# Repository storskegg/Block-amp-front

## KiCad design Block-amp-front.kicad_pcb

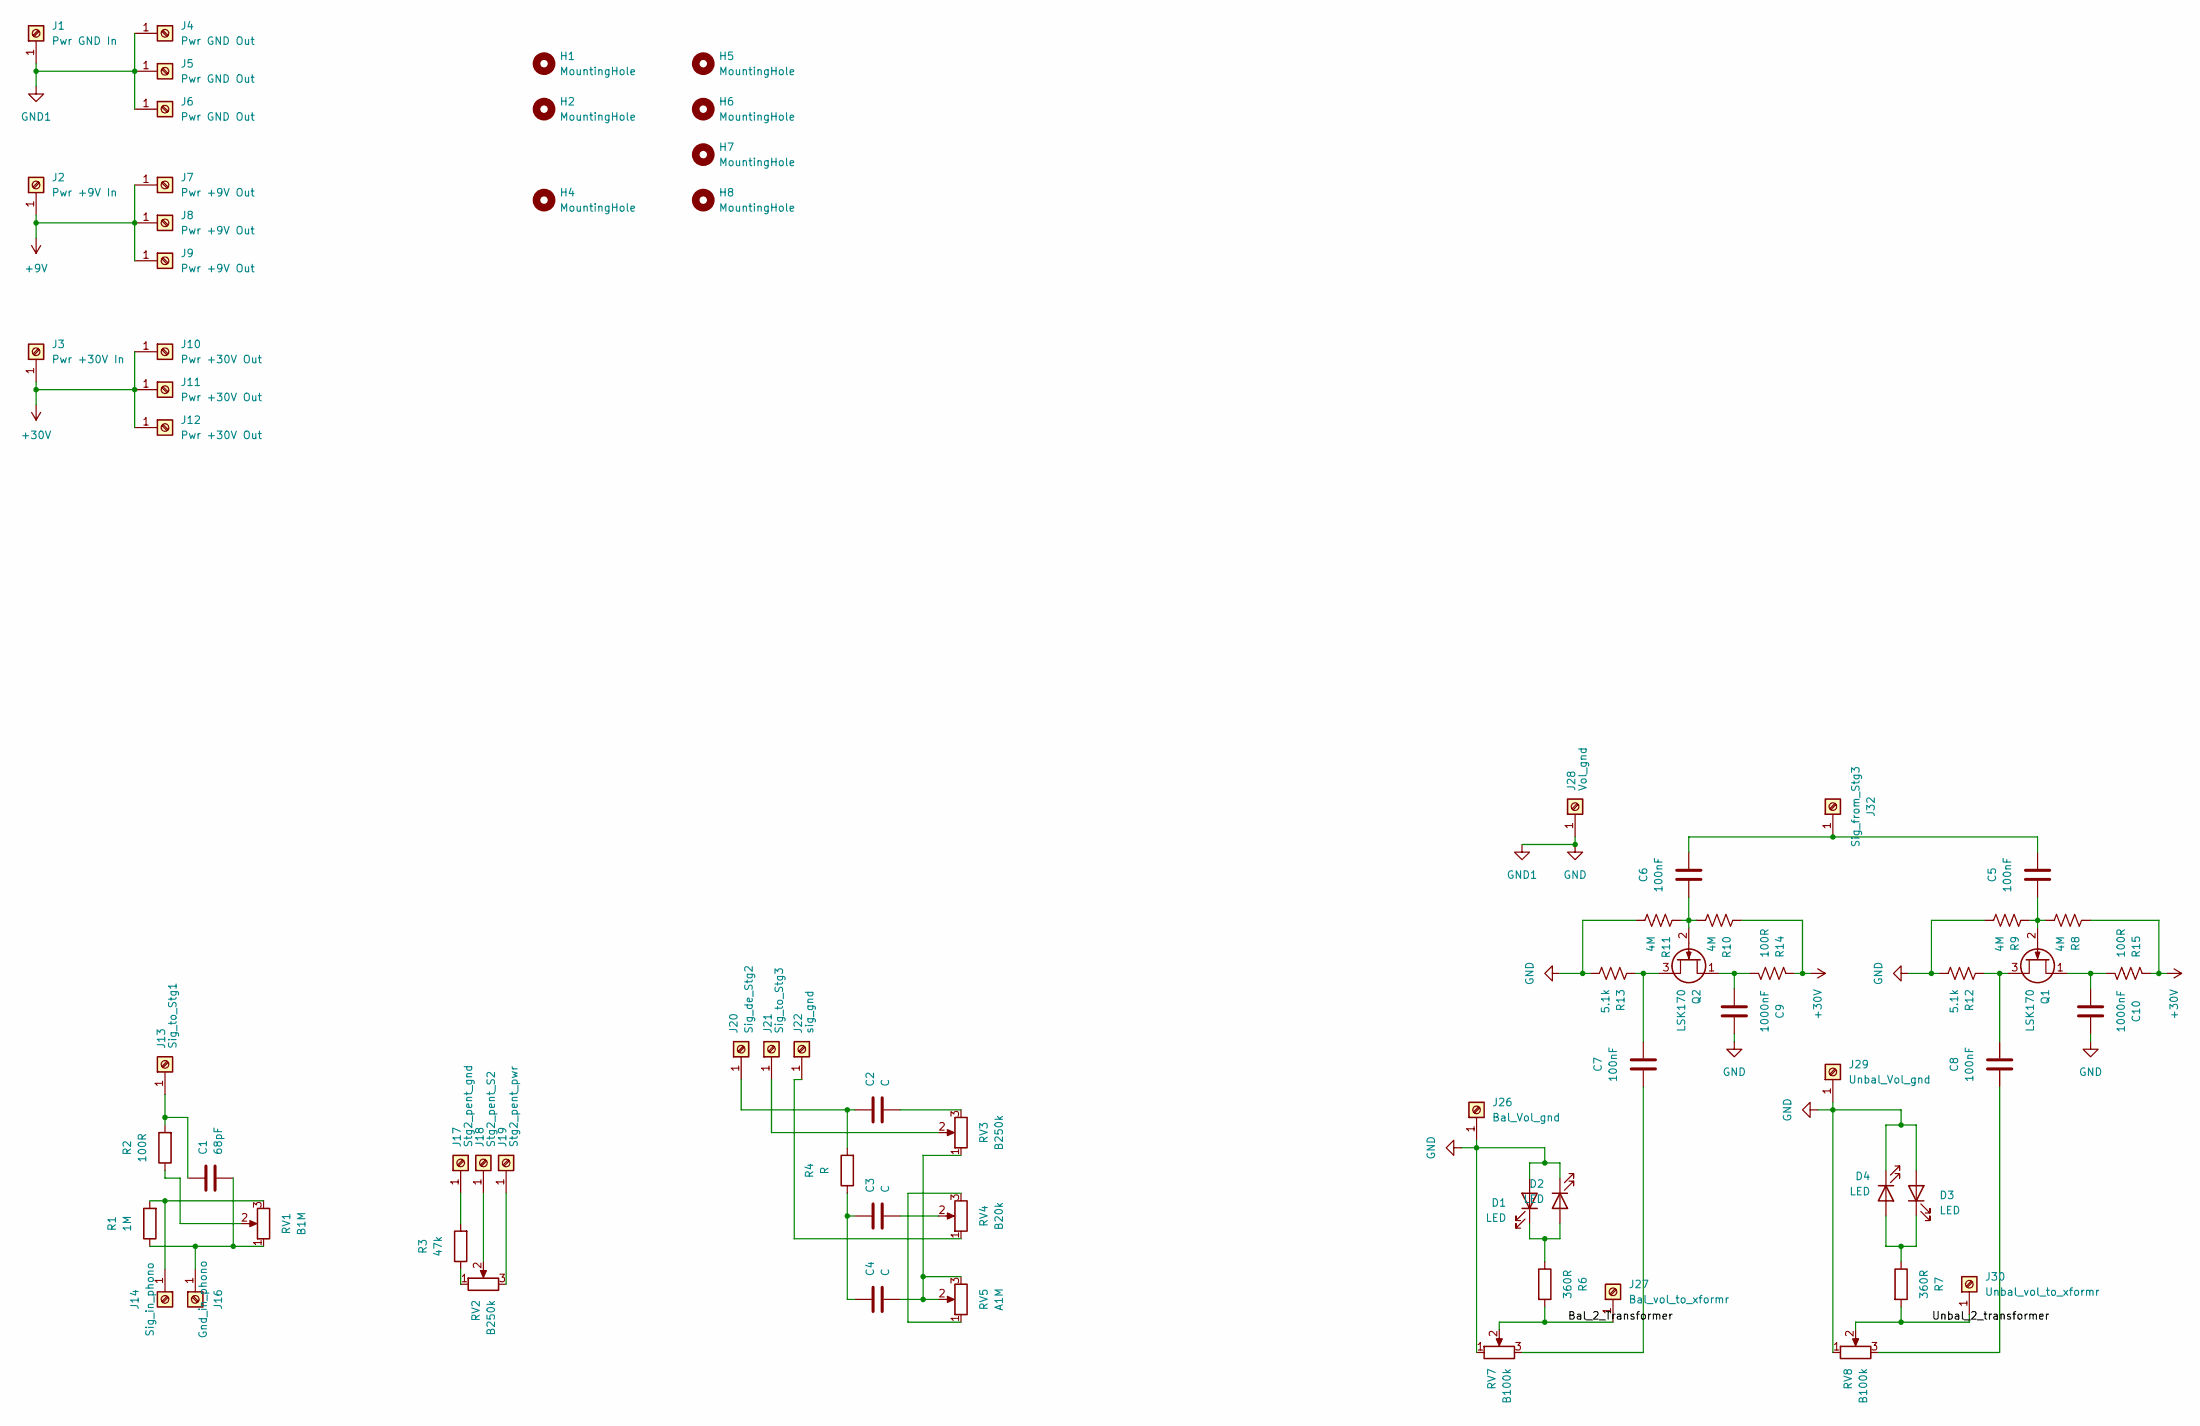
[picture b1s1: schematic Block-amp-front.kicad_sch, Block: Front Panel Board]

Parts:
C1: 68pF; C_Rect_L7.0mm_W3.5mm_P2.50mm_P5.00mm
C2, C3, C4: C; C_Rect_L7.0mm_W3.5mm_P2.50mm_P5.00mm
C5, C6, C7, C8: 100nF; C_Disc_D4.3mm_W1.9mm_P5.00mm
C9, C10: 1000nF; C_Disc_D7.5mm_W5.0mm_P5.00mm
D1, D2, D3, D4: LED; LED_D5.0mm_Clear
H1, H2, H4, H5, H6, H7, H8: MountingHole; MountingHole_2.2mm_M2
J1: Pwr GND In; Pin_D1.1mm_L8.5mm_W2.5mm_FlatFork
J2: Pwr +9V In; Pin_D1.1mm_L8.5mm_W2.5mm_FlatFork
J3: Pwr +30V In; Pin_D1.1mm_L8.5mm_W2.5mm_FlatFork
J4, J5, J6: Pwr GND Out; Pin_D1.1mm_L8.5mm_W2.5mm_FlatFork
J7, J8, J9: Pwr +9V Out; Pin_D1.1mm_L8.5mm_W2.5mm_FlatFork
J10, J11, J12: Pwr +30V Out; Pin_D1.1mm_L8.5mm_W2.5mm_FlatFork
J13: Sig_to_Stg1; Pin_D1.1mm_L8.5mm_W2.5mm_FlatFork
J14: Sig_in_phono; Pin_D1.1mm_L8.5mm_W2.5mm_FlatFork
J16: Gnd_in_phono; Pin_D1.1mm_L8.5mm_W2.5mm_FlatFork
J17: Stg2_pent_gnd; Pin_D1.1mm_L8.5mm_W2.5mm_FlatFork
J18: Stg2_pent_S2; Pin_D1.1mm_L8.5mm_W2.5mm_FlatFork
J19: Stg2_pent_pwr; Pin_D1.1mm_L8.5mm_W2.5mm_FlatFork
J20: Sig_de_Stg2; Pin_D1.1mm_L8.5mm_W2.5mm_FlatFork
J21: Sig_to_Stg3; Pin_D1.1mm_L8.5mm_W2.5mm_FlatFork
J22: sig_gnd; Pin_D1.1mm_L8.5mm_W2.5mm_FlatFork
J26: Bal_Vol_gnd; Pin_D1.1mm_L8.5mm_W2.5mm_FlatFork
J27: Bal_vol_to_xformr; Pin_D1.1mm_L8.5mm_W2.5mm_FlatFork
J28: Vol_gnd; Pin_D1.1mm_L8.5mm_W2.5mm_FlatFork
J29: Unbal_Vol_gnd; Pin_D1.1mm_L8.5mm_W2.5mm_FlatFork
J30: Unbal_vol_to_xformr; Pin_D1.1mm_L8.5mm_W2.5mm_FlatFork
J32: Sig_from_Stg3; Pin_D1.1mm_L8.5mm_W2.5mm_FlatFork
Q1, Q2: LSK170; TO-92_Inline_Wide
R1: 1M; R_Axial_DIN0207_L6.3mm_D2.5mm_P10.16mm_Horizontal
R2, R14, R15: 100R; R_Axial_DIN0207_L6.3mm_D2.5mm_P10.16mm_Horizontal
R3: 47k; R_Axial_DIN0207_L6.3mm_D2.5mm_P10.16mm_Horizontal
R4: R; R_Axial_DIN0207_L6.3mm_D2.5mm_P10.16mm_Horizontal
R6, R7: 360R; R_Axial_DIN0204_L3.6mm_D1.6mm_P7.62mm_Horizontal
R8, R9, R10, R11: 4M; R_Axial_DIN0207_L6.3mm_D2.5mm_P10.16mm_Horizontal
R12, R13: 5.1k; R_Axial_DIN0207_L6.3mm_D2.5mm_P10.16mm_Horizontal
RV1: B1M; Potentiometer_Alps_RK163_Single_Horizontal
RV2, RV3: B250k; Potentiometer_Alps_RK163_Single_Horizontal
RV4: B20k; Potentiometer_Alps_RK163_Single_Horizontal
RV5: A1M; Potentiometer_Alps_RK163_Single_Horizontal
RV7, RV8: B100k; Potentiometer_Alps_RK163_Single_Horizontal

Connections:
+9V: J2.1, J7.1, J8.1, J9.1
+30V: J3.1, J10.1, J11.1, J12.1, R8.1, R10.1, R14.1, R15.1
/Bal_2_Transformer: J27.1, R6.2, RV7.2
/Unbal_2_transformer: J30.1, R7.2, RV8.2
GND: C9.1, C10.1, D1.2 (A), D2.1 (K), D3.2 (A), D4.1 (K), J1.1, J4.1, J5.1, J6.1, J26.1, J28.1, J29.1, R9.2, R11.2, R12.2, R13.2, RV7.1, RV8.1
unnamed: C2.2, RV3.3
unnamed: C3.1, C4.1, R4.1
unnamed: C3.2, RV4.2
unnamed: C4.2, RV3.1, RV5.2, RV5.3
unnamed: C7.1, RV7.3
unnamed: C8.1, RV8.3
unnamed: D1.1 (K), D2.2 (A), R6.1
unnamed: D3.1 (K), D4.2 (A), R7.1
unnamed: C1.1, J13.1, R2.2
unnamed: J14.1, R1.2, RV1.3
unnamed: C1.2, J16.1, R1.1, RV1.1
unnamed: J17.1, R3.2
unnamed: J18.1, RV2.2
unnamed: J19.1, RV2.3
unnamed: C2.1, J20.1, R4.2
unnamed: J21.1, RV3.2
unnamed: J22.1, RV4.1
unnamed: C5.2, C6.2, J32.1
unnamed: C10.2, Q1.1 (D), R15.2
unnamed: C5.1, Q1.2 (G), R8.2, R9.1
unnamed: C8.2, Q1.3 (S), R12.1
unnamed: C9.2, Q2.1 (D), R14.2
unnamed: C6.1, Q2.2 (G), R10.2, R11.1
unnamed: C7.2, Q2.3 (S), R13.1
unnamed: R2.1, RV1.2
unnamed: R3.1, RV2.1
unnamed: RV4.3, RV5.1

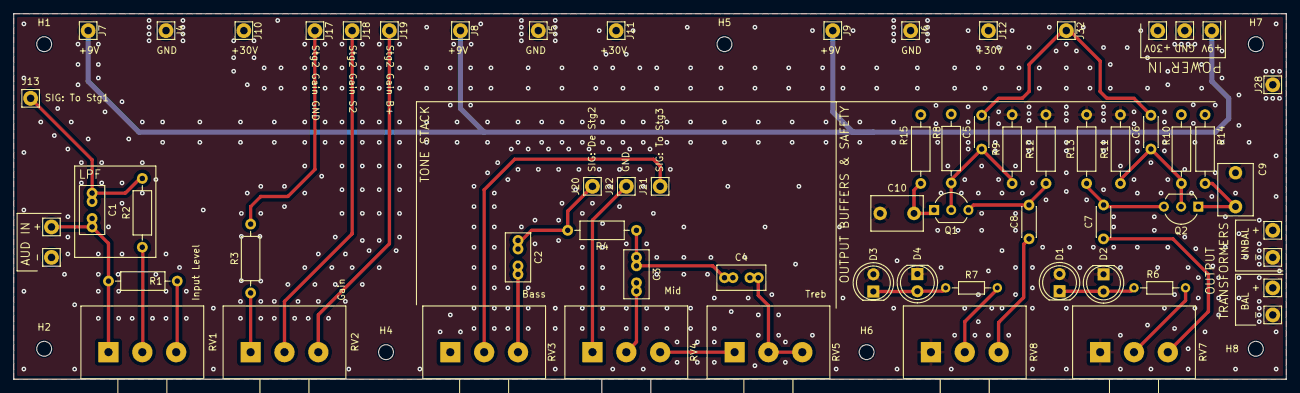
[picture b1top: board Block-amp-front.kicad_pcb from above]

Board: 6 copper layers, 188.0 x 54.0 mm, 71 parts (0 on the bottom side), 32 nets.

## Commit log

2025-03-07 v1.0
